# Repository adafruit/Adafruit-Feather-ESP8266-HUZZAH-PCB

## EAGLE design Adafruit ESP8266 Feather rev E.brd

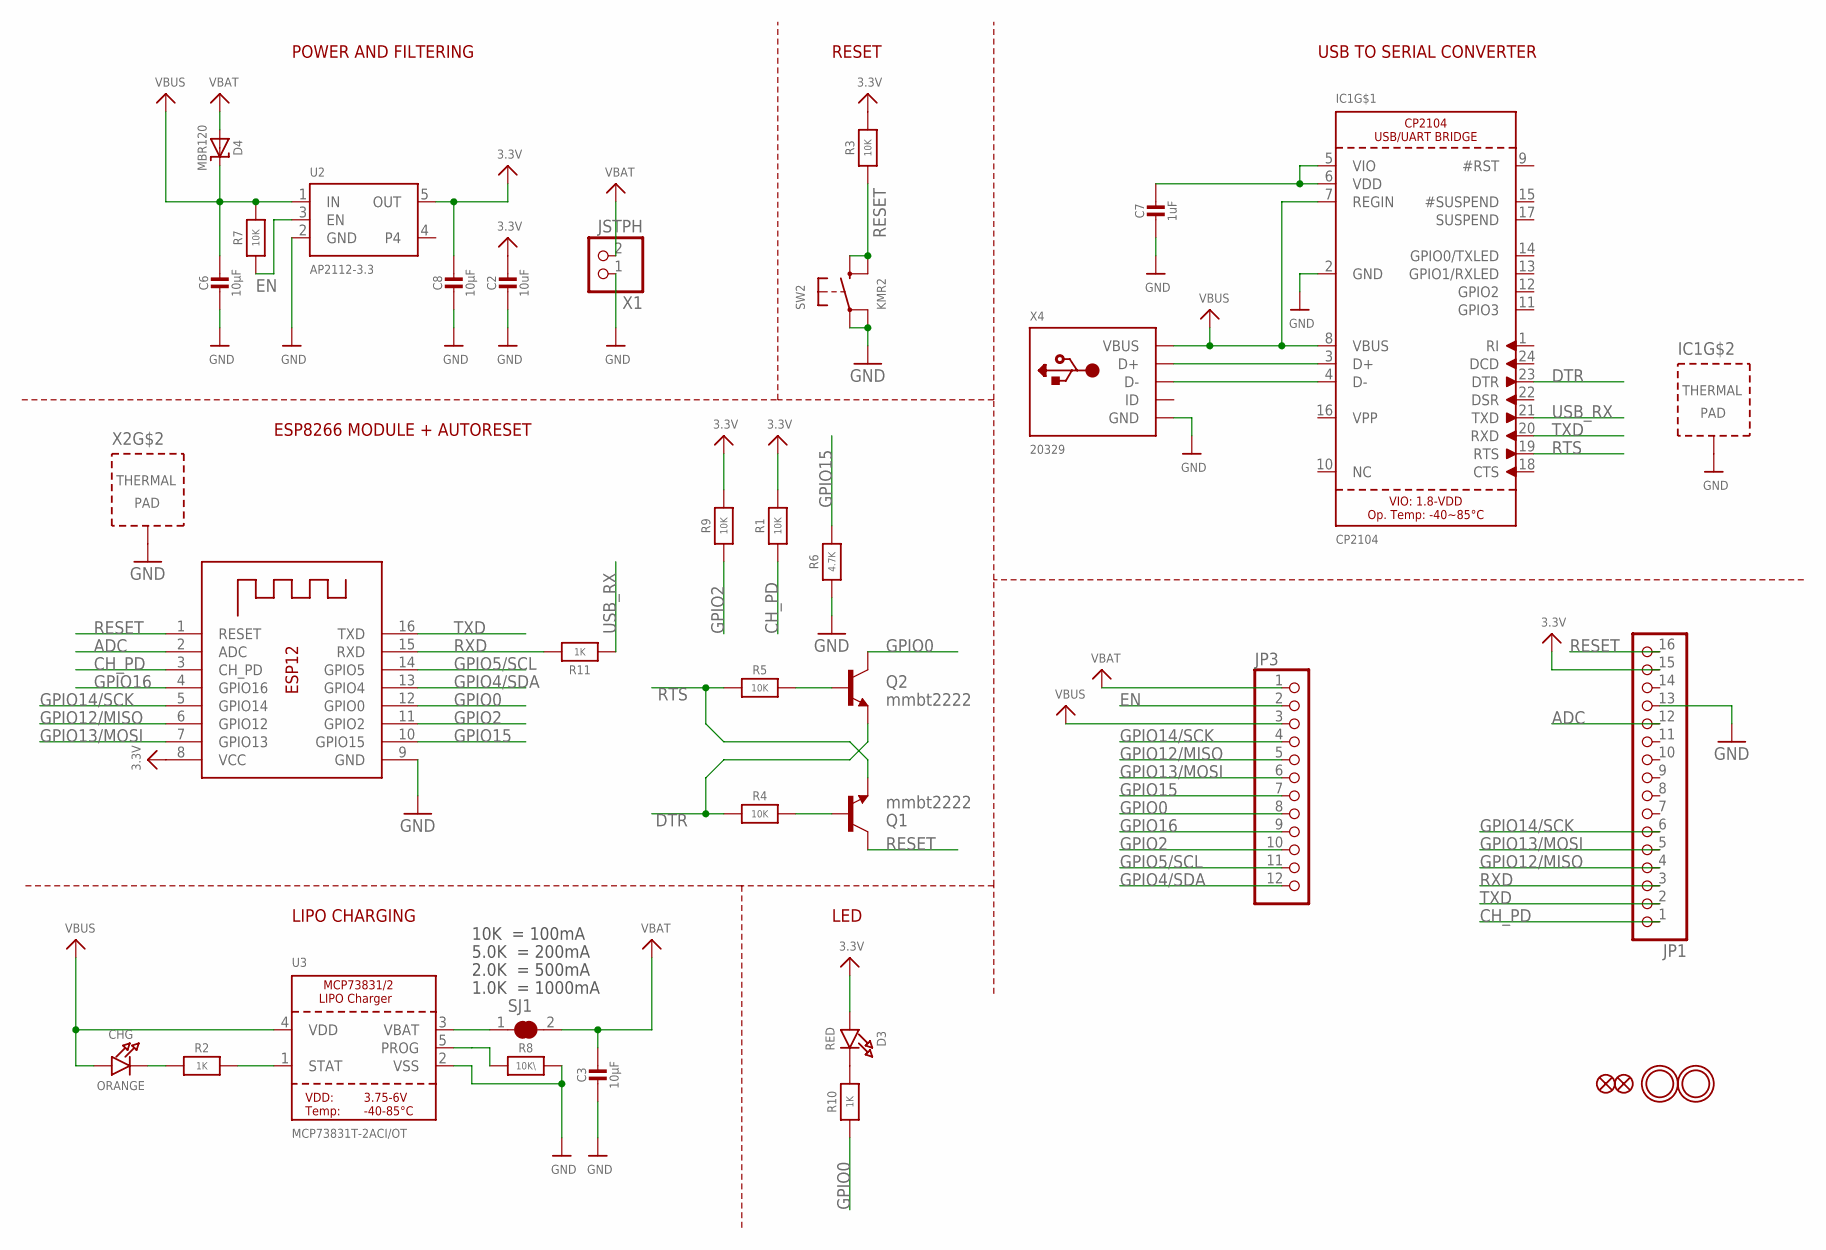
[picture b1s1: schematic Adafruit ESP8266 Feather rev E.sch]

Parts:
C2: 10uF; 0805-NO
C3, C6, C8: 10µF; 0805-NO
C7: 1uF; 0603-NO
CHG: ORANGE; CHIPLED_0805_NOOUTLINE
D3: RED; CHIPLED_0805_NOOUTLINE
D4: MBR120; SOD-123
IC1: CP2104; QFN24_4MM_SMSC
JP1: HEADER-1X16ROUND; 1X16_ROUND
JP3: HEADER-1X12; 1X12_ROUND
Q1, Q2: mmbt2222; SOT23-3
R1, R3, R4, R5, R7, R9: 10K; 0603-NO
R2, R10: 1K; 0603-NO
R6: 4.7K; 0603-NO
R8: 10K\; 0603-NO
R11: 1K; _0603MP
SJ1: SOLDERJUMPER_CLOSED; SOLDERJUMPER_CLOSEDWIRE
SW2: KMR2; BTN_KMR2_4.6X2.8
U2: AP2112-3.3; SOT23-5
U3: MCP73831T-2ACI/OT; SOT23-5
U$31, U$32: MOUNTINGHOLE2.5; MOUNTINGHOLE_2.5_PLATED
U$34, U$35: FIDUCIAL_1MM
X1: JSTPH; JSTPH2
X2: ESP-12; ESP-12S
X4: 20329; 4UCONN_20329_V2

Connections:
3.3V: C2.1, C8.1, D3.A, JP1.15, R1.2, R3.2, R9.2, U2.5 (OUT), X2.8 (VCC)
ADC: JP1.12, X2.2 (ADC)
CH_PD: JP1.1, R1.1, X2.3 (CH_PD)
DTR: IC1.23 (DTR), Q2.2 (E), R4.1
EN: JP3.2, R7.1, U2.3 (EN)
GND: C2.2, C3.2, C6.2, C7.2, C8.2, IC1.2 (GND), IC1.THERM (TP), JP1.13, R6.1, R8.2, SW2.A, SW2.A' (P1), U2.2 (GND), U3.2 (VSS), X1.1, X2.9 (GND), X2.P$1 (TP), X4.BASE@1 (GND), X4.BASE@2 (GND), X4.GND, X4.SPRT@1 (GND), X4.SPRT@2 (GND), X4.SPRT@3 (GND), X4.SPRT@4 (GND)
GPIO0: JP3.8, Q2.3 (C), R10.1, X2.12 (GPIO0)
GPIO2: JP3.10, R9.1, X2.11 (GPIO2)
GPIO4/SDA: JP3.12, X2.13 (GPIO4)
GPIO5/SCL: JP3.11, X2.14 (GPIO5)
GPIO12/MISO: JP1.4, JP3.5, X2.6 (GPIO12)
GPIO13/MOSI: JP1.5, JP3.6, X2.7 (GPIO13)
GPIO14/SCK: JP1.6, JP3.4, X2.5 (GPIO14)
GPIO15: JP3.7, R6.2, X2.10 (GPIO15)
GPIO16: JP3.9, X2.4 (GPIO16)
unnamed: CHG.C, R2.1
unnamed: IC1.3 (D+), X4.D+
unnamed: R2.2, U3.1 (STAT)
unnamed: R8.1, U3.5 (PROG)
unnamed: D3.C, R10.2
unnamed: IC1.4 (D-), X4.D-
unnamed: SJ1.1, U3.3 (VBAT)
unnamed: C7.1, IC1.5 (VIO), IC1.6 (VDD)
unnamed: Q1.1 (B), R4.2
unnamed: Q2.1 (B), R5.2
RESET: JP1.16, Q1.3 (C), R3.1, SW2.B (S), SW2.B' (S1), X2.1 (RESET)
RTS: IC1.19 (RTS), Q1.2 (E), R5.1
RXD: JP1.3, R11.2, X2.15 (RXD)
TXD: IC1.20 (RXD), JP1.2, X2.16 (TXD)
USB_RX: IC1.21 (TXD), R11.1
VBAT: C3.1, D4.A, JP3.1, SJ1.2, X1.2
VBUS: C6.1, CHG.A, D4.C, IC1.7 (REGIN), IC1.8 (VBUS), JP3.3, R7.2, U2.1 (IN), U3.4 (VDD), X4.VBUS

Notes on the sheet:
POWER AND FILTERING
RESET
10K = 100mA
5.0K = 200mA
2.0K = 500mA
1.0K = 1000mA
USB TO SERIAL CONVERTER
LIPO CHARGING
LED
ESP8266 MODULE + AUTORESET

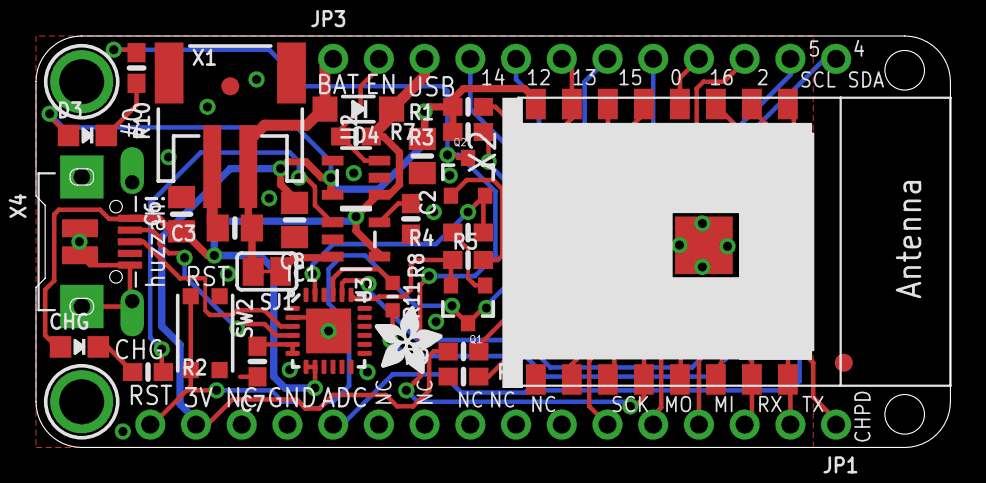
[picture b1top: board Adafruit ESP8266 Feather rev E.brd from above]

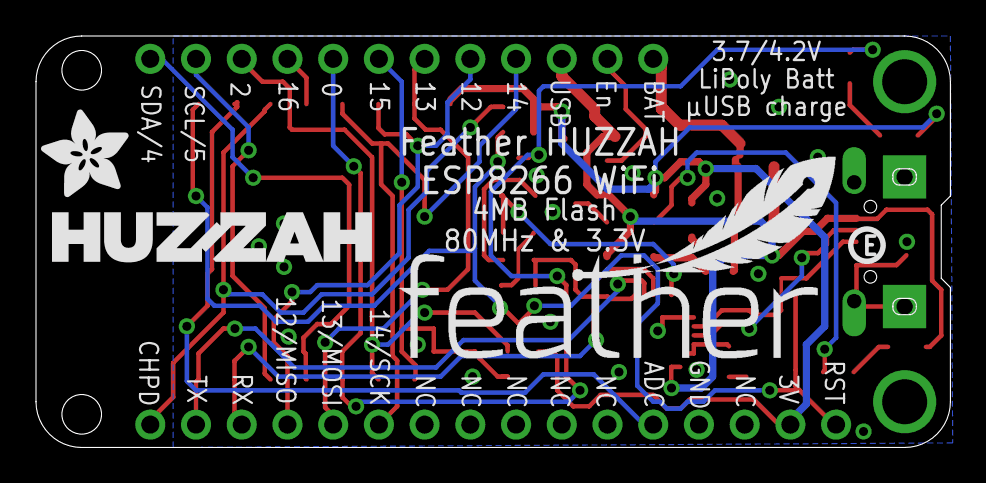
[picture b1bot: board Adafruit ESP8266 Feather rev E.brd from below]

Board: 2 copper layers, 50.8 x 22.9 mm, 40 parts (4 on the bottom side), 32 nets.

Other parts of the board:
U$7: ADAFRUIT_5MM
U$9: FEATHERLOGO
U$13: PCBFEAT-REV-040
U$15: ADAFRUIT_3.5MM
U$23: HUZZAHLOGO

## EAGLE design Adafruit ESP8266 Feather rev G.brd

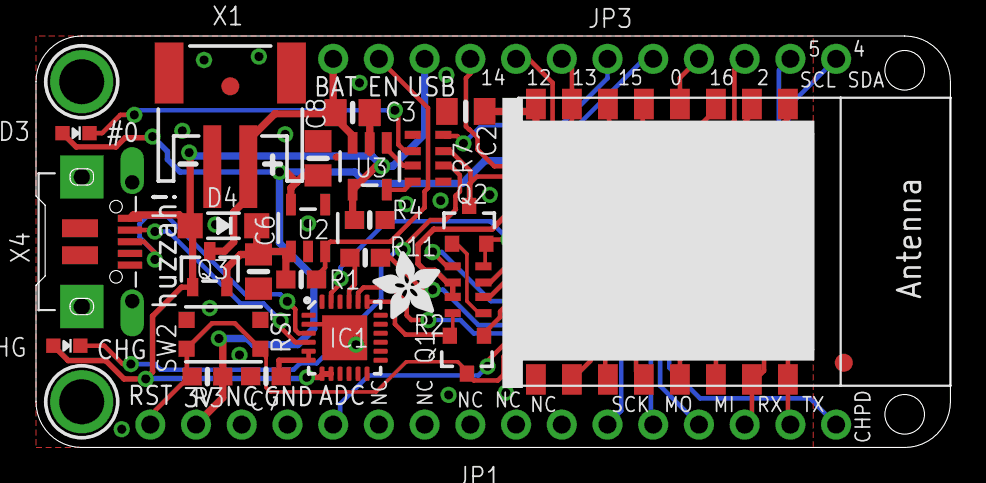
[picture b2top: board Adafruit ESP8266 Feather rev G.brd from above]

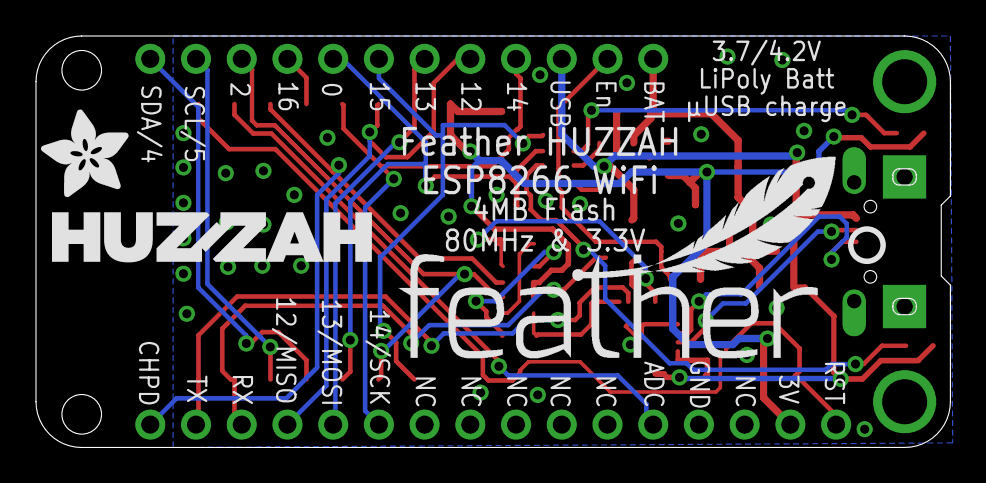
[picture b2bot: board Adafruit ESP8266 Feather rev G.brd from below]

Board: 2 copper layers, 50.8 x 22.9 mm, 35 parts (4 on the bottom side), 32 nets.

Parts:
C2: 10uF; 0805_10MGAP
C3, C6, C8: 10µF; 0805-NO
C7: 1uF; 0603-NO
CHG: ORANGE; CHIPLED_0603_NOOUTLINE
D3: RED; CHIPLED_0603_NOOUTLINE
D4: MBR0540; SOD-123
IC1: CP2104; QFN24_4MM_SMSC
JP1: 1X16_ROUND
JP3: 1X12_ROUND
Q1, Q2: mmbt2222; SOT23-3
Q3: DMG341; SOT23-R
R1: 10k; 0603-NO
R2: 10K; RESPACK_4X0603_NO
R3: 10K; 0603-NO
R4: 100K; 0603-NO
R7: 4.7K; RESPACK_4X0603_NO
R11: 1K; 0603-NO
SW2: KMR2; BTN_KMR2_4.6X2.8
U2: AP2112-3.3; SOT23-5
U3: MCP73831T-2ACI/OT; SOT23-5
U$7: ADAFRUIT_5MM
U$9: FEATHERLOGO
U$13: PCBFEAT-REV-040
U$15: ADAFRUIT_3.5MM
U$23: HUZZAHLOGO
U$31, U$32: MOUNTINGHOLE2.5; MOUNTINGHOLE_2.5_PLATED
U$34, U$35: FIDUCIAL_1MM
X1: JSTPH; JSTPH2_BATT
X3: ESP-12F
X4: 20329; 4UCONN_20329_V2

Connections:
3.3V: C2.1, C8.1, D3.A, JP1.15, R2.6, R2.7, R3.2, U2.5, X3.8
ADC: JP1.12, X3.2
CH_PD: JP1.1, R2.3, X3.3
DTR: IC1.23, Q2.2, R2.4
EN: JP3.2, R1.1, U2.3
GND: C2.2, C3.2, C6.2, C7.2, C8.2, IC1.2, IC1.THERM, JP1.13, R4.1, R7.1, R7.5, SW2.A, SW2.A', U2.2, U3.2, X1.1, X3.9, X4.BASE@1, X4.BASE@2, X4.GND, X4.SPRT@1, X4.SPRT@2, X4.SPRT@3, X4.SPRT@4
GPIO0: JP3.8, Q2.3, R7.7, X3.12
GPIO2: JP3.10, R2.2, X3.11
GPIO4/SDA: JP3.12, X3.13
GPIO5/SCL: JP3.11, X3.14
GPIO12/MISO: JP1.4, JP3.5, X3.6
GPIO13/MOSI: JP1.5, JP3.6, X3.7
GPIO14/SCK: JP1.6, JP3.4, X3.5
GPIO15: JP3.7, R7.8, X3.10
GPIO16: JP3.9, X3.4
unnamed: CHG.C, R7.6
unnamed: IC1.3, X4.D+
unnamed: R7.3, U3.1
unnamed: R7.4, U3.5
unnamed: D3.C, R7.2
unnamed: IC1.4, X4.D-
unnamed: C7.1, IC1.5, IC1.6
unnamed: Q1.1, R2.5
unnamed: Q2.1, R2.1
RESET: JP1.16, Q1.3, R3.1, SW2.B, SW2.B', X3.1
RTS: IC1.19, Q1.2, R2.8
RXD: JP1.3, R11.2, X3.15
TXD: IC1.20, JP1.2, X3.16
USB_RX: IC1.21, R11.1
VBAT: C3.1, JP3.1, Q3.3, U3.3, X1.2
VBUS: CHG.A, D4.A, IC1.7, IC1.8, JP3.3, Q3.1, R4.2, U3.4, X4.VBUS
VHI: C6.1, D4.C, Q3.2, R1.2, U2.1

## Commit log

2018-04-06 USB: Replacing USB port with an obtainable one
    The 4UCONN connector used here isn't easily obtained anymore
    and makes it hard for derivative boards to get built without
    issues. Replacing with the Amphenol FCI 10118193-0001LF which
    is cheap and easily obtained.
2019-01-05 https://github.com/adafruit/Adafruit-Feather-ESP8266-HUZZAH-PCB/issues/2
2019-07-16 updated to use cookiecutter for pcb repos
2020-10-30 new rev!

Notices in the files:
parts and their libraries:
microbuilder: This work is placed in the public domain, and may be freely used for commercial and non-commercial work with the following conditions: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
SparkFun: Licensing: CC v3.0 Share-Alike You are welcome to use this library for commercial purposes.
